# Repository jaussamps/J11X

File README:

This is a basic analog test rig for J112/3 JFETs, for determining
     V_GS(off) and I_DSS of specific samples. The design can easily be
     modified to test other N-type depletion-mode families by changing
     power rails, etc. as needed to account for their characteristics.

     As always, this design is free for you to use as you see fit, but
     you do so at your own risk: I provide no warranties of any kind.

                                     --- Charles E. Youse (@jaussamps)

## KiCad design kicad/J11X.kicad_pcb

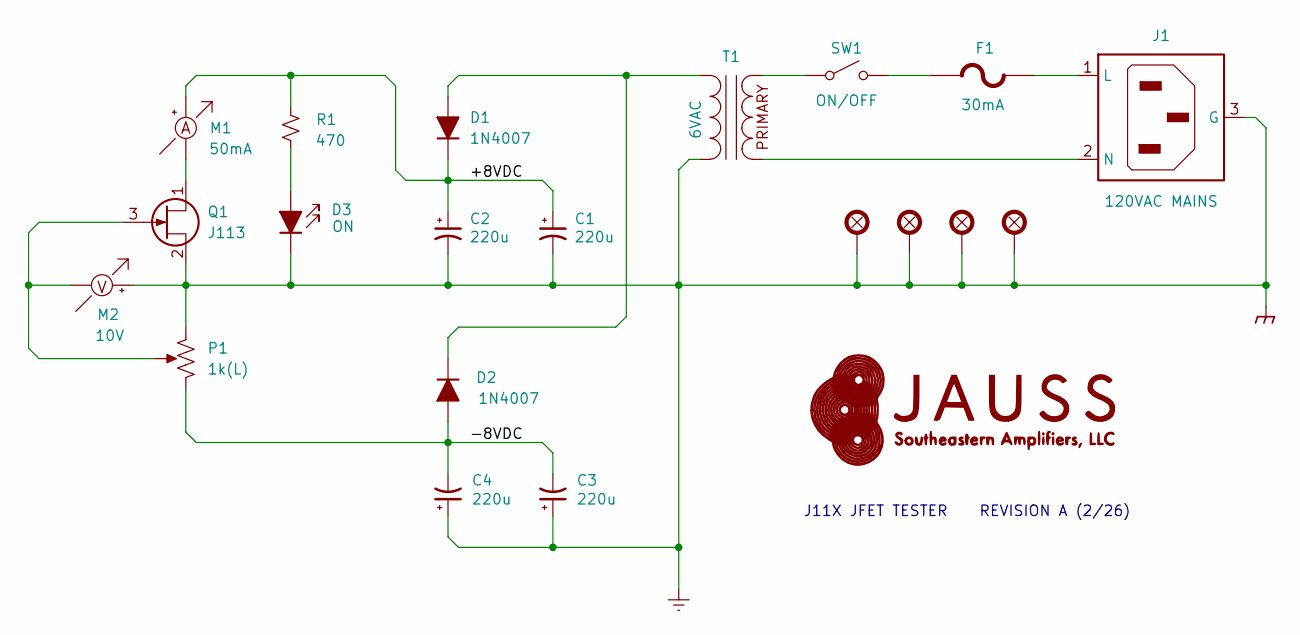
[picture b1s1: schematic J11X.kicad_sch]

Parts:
C1, C2, C3, C4: 220u; C-POL-RAD-6.3X2.5
D1, D2: 1N4007; D-DO41
D3: LED; D-LITEON-LTL-4233
F1: 30mA; F-YAGEO-BK250-030-DZ
G1: LOGO
H1, H2, H3, H4: H-NO-6-METAL
J1: J-ONSHORE-OSTTC032162
M1: 50mA; J-ONSHORE-OSTTC022162
M2: 10V; J-ONSHORE-OSTTC022162
P1: 1k(L); J-ONSHORE-OSTTC032162
Q1: J113; Q-TO92-WIDE
R1: 470; R-TECONN-ROX1S
SW1: J-ONSHORE-OSTTC022162
T1: 6VAC; T-ZETTLER-BV201S06003A

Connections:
/+8VDC: C1.1, C2.1, D1.1 (K), M1.1 (+), R1.1
/-8VDC: C3.2, C4.2, D2.2 (A), P1.3
=CHASSIS: C1.2, C2.2, C3.1, C4.1, D3.1 (K), H1.1, H2.1, H3.1, H4.1, J1.3 (G), M2.1 (+), P1.1, Q1.2 (S), T1.4 (S)
unnamed: D1.2 (A), D2.1 (K), T1.3 (S)
unnamed: D3.2 (A), R1.2
unnamed: F1.1 (A), SW1.2 (B)
unnamed: F1.2 (B), J1.1 (L)
unnamed: J1.2 (N), T1.2
unnamed: M1.2 (-), Q1.1 (D)
unnamed: M2.2 (-), P1.2, Q1.3 (G)
unnamed: SW1.1 (A), T1.1

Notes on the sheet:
J11X JFET TESTER REVISION A (2/26)

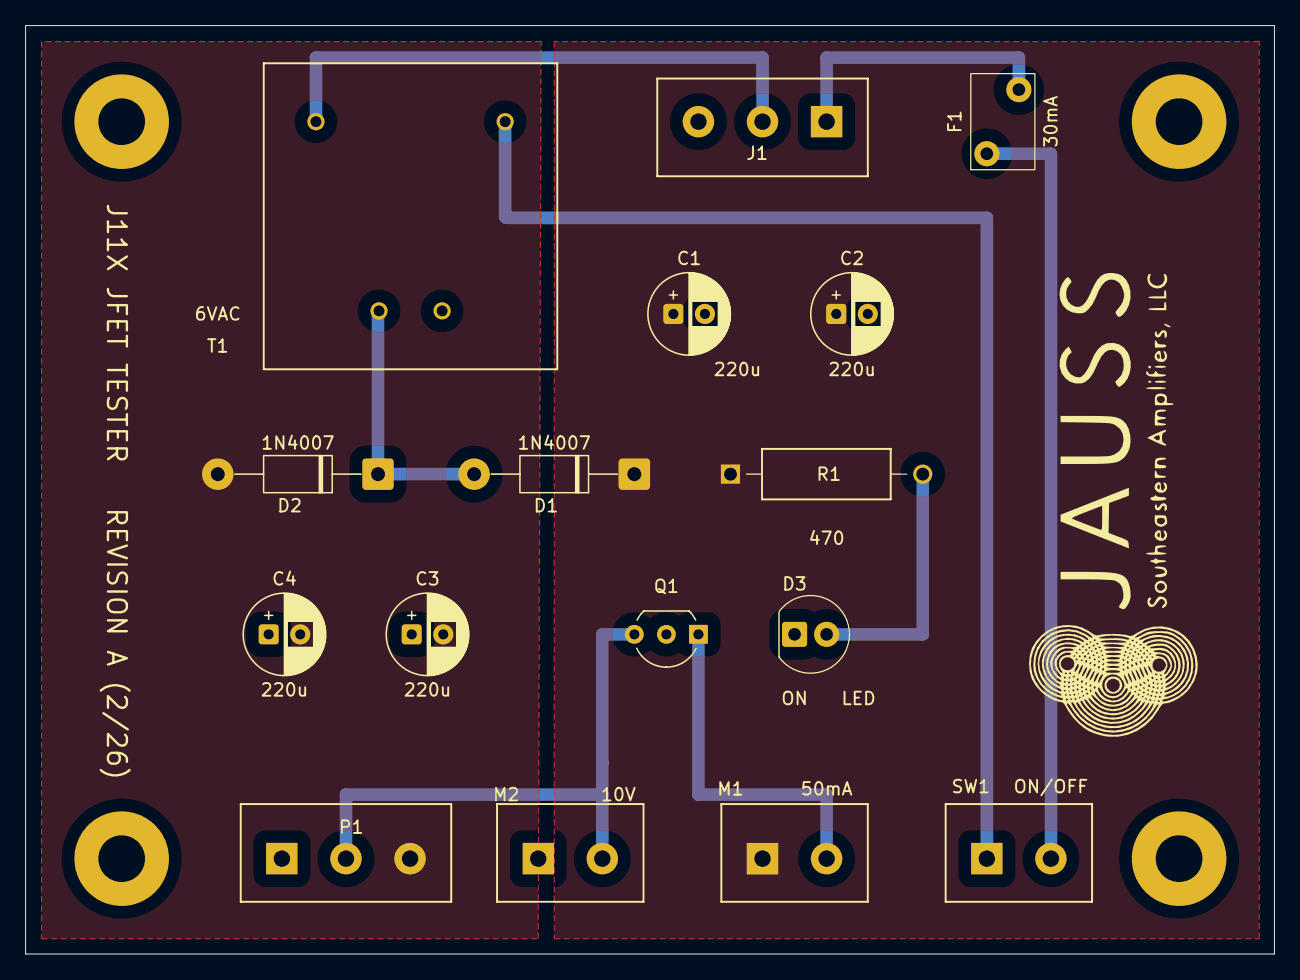
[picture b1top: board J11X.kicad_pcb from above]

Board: 2 copper layers, 99.0 x 73.6 mm, 21 parts (0 on the bottom side), 11 nets.

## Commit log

2026-02-27 REVISION A (2/26)
    [IN PROGRESS]
